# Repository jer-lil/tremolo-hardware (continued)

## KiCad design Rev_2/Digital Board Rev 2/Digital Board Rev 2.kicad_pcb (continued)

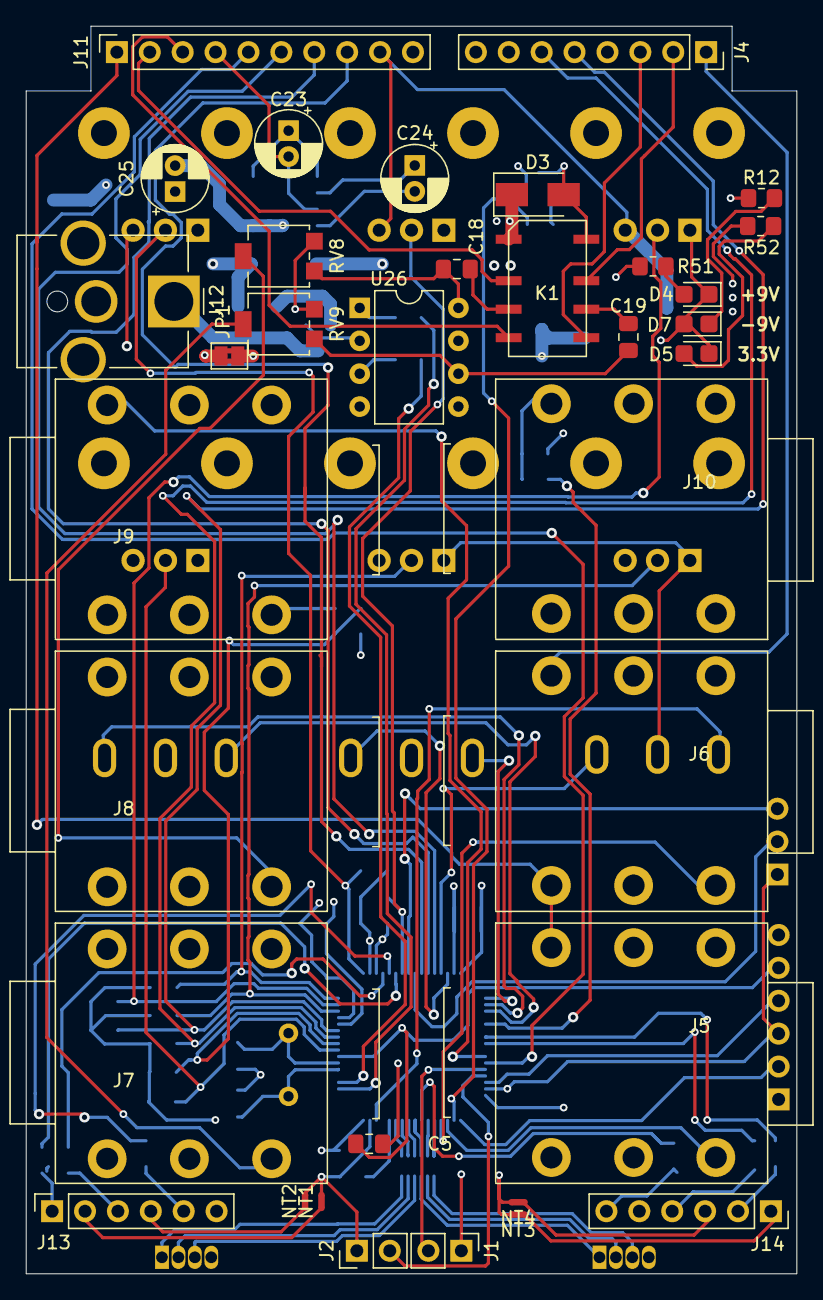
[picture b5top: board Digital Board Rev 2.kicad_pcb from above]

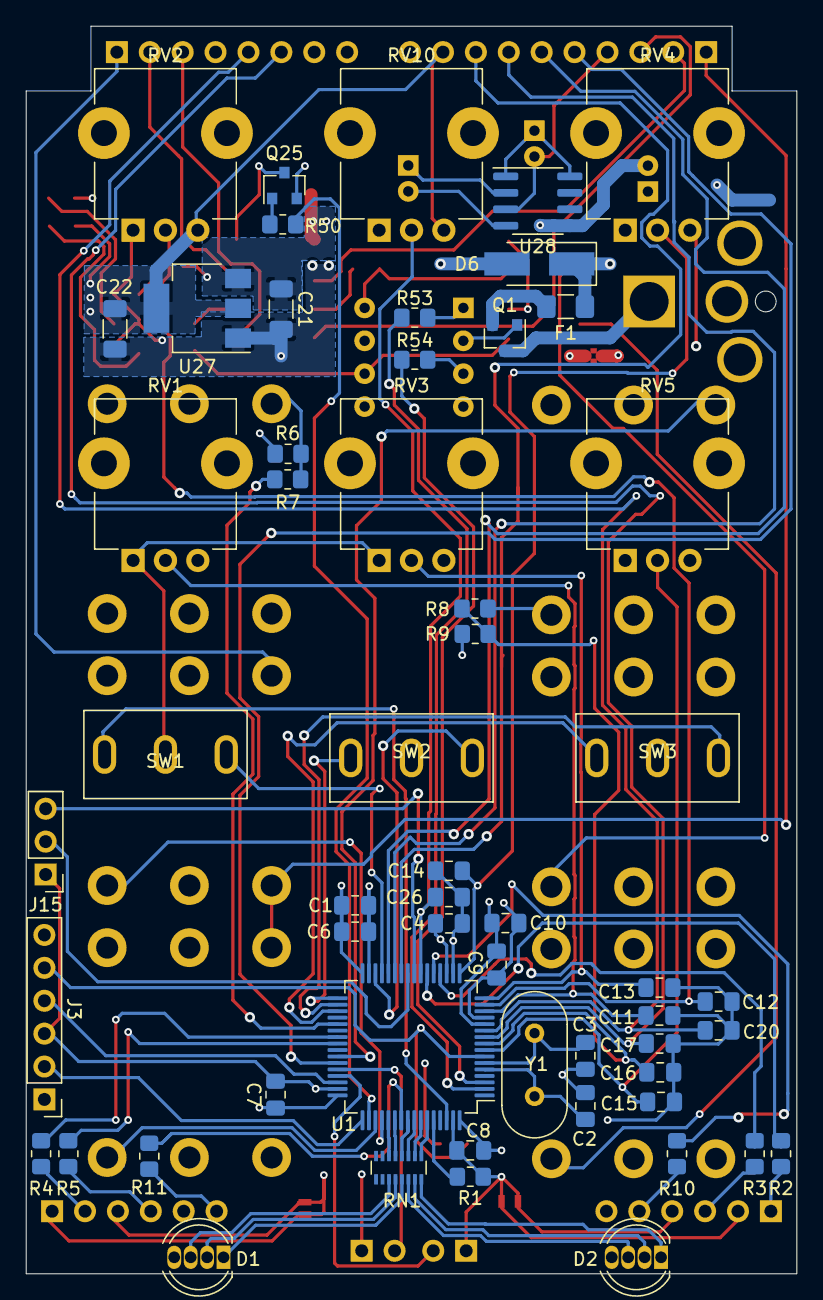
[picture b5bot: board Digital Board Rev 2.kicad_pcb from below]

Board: 4 copper layers, 59.5 x 96.3 mm, 91 parts (56 on the bottom side), 94 nets.

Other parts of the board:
D1, D2: LED_RGBA; LED_D5.0mm-4_RGB
RN1: R_Pack08; R_Array_Convex_8x0602
U26: TLP222A-2; DIP-8_W7.62mm

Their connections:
+3V3: D1.4, D2.4; also elsewhere on the board
/Audio Jacks/CH1_OUT_PRE: U26.8; also elsewhere on the board
/Audio Jacks/CH2_OUT_PRE: U26.6; also elsewhere on the board
/LED1_B: RN1.6; also elsewhere on the board
/LED1_G: RN1.5; also elsewhere on the board
/LED1_R: RN1.4; also elsewhere on the board
/LED2_B: RN1.3; also elsewhere on the board
/LED2_G: RN1.2; also elsewhere on the board
/LED2_R: RN1.1; also elsewhere on the board
/LEDs/B1_R: D1.3, RN1.11
/LEDs/B2_R: D2.3, RN1.14
/LEDs/G1_R: D1.2, RN1.12
/LEDs/G2_R: D2.2, RN1.15
/LEDs/R1_R: D1.1, RN1.13
/LEDs/R2_R: D2.1, RN1.16
GNDA: U26.5, U26.7; also elsewhere on the board
GNDD: U26.2, U26.4; also elsewhere on the board
unnamed 115: U26.1; also elsewhere on the board
unnamed 116: U26.3; also elsewhere on the board

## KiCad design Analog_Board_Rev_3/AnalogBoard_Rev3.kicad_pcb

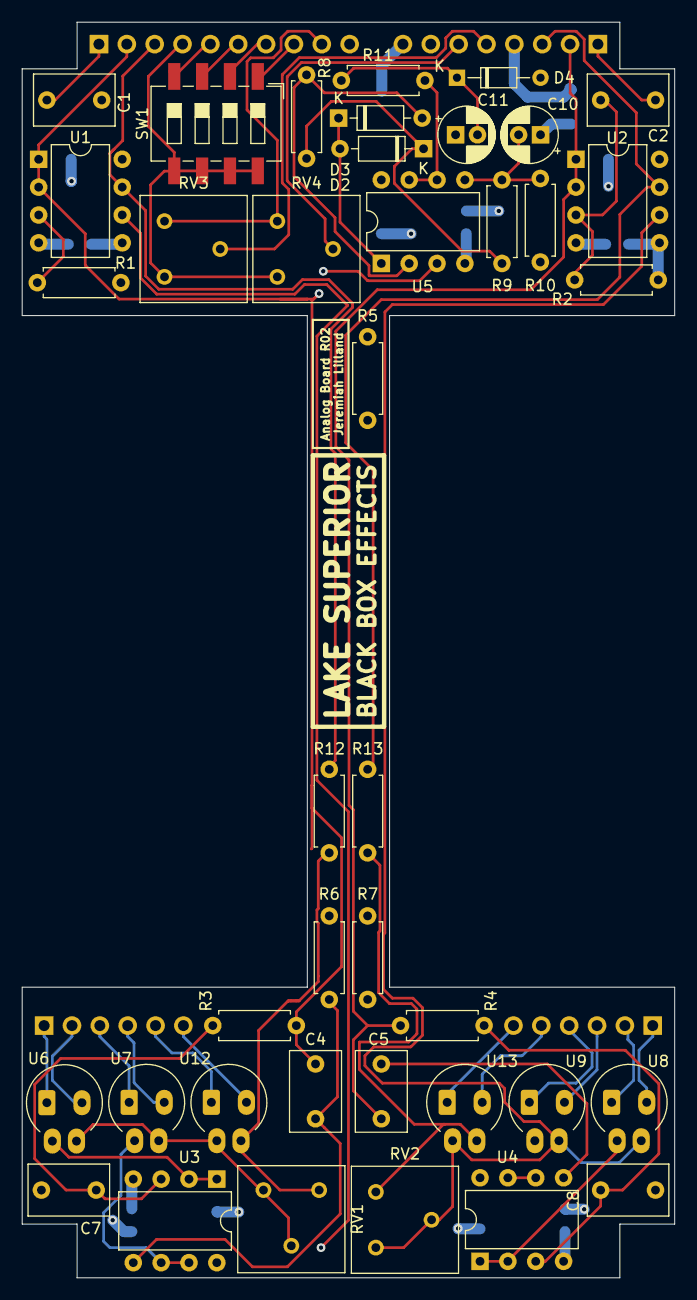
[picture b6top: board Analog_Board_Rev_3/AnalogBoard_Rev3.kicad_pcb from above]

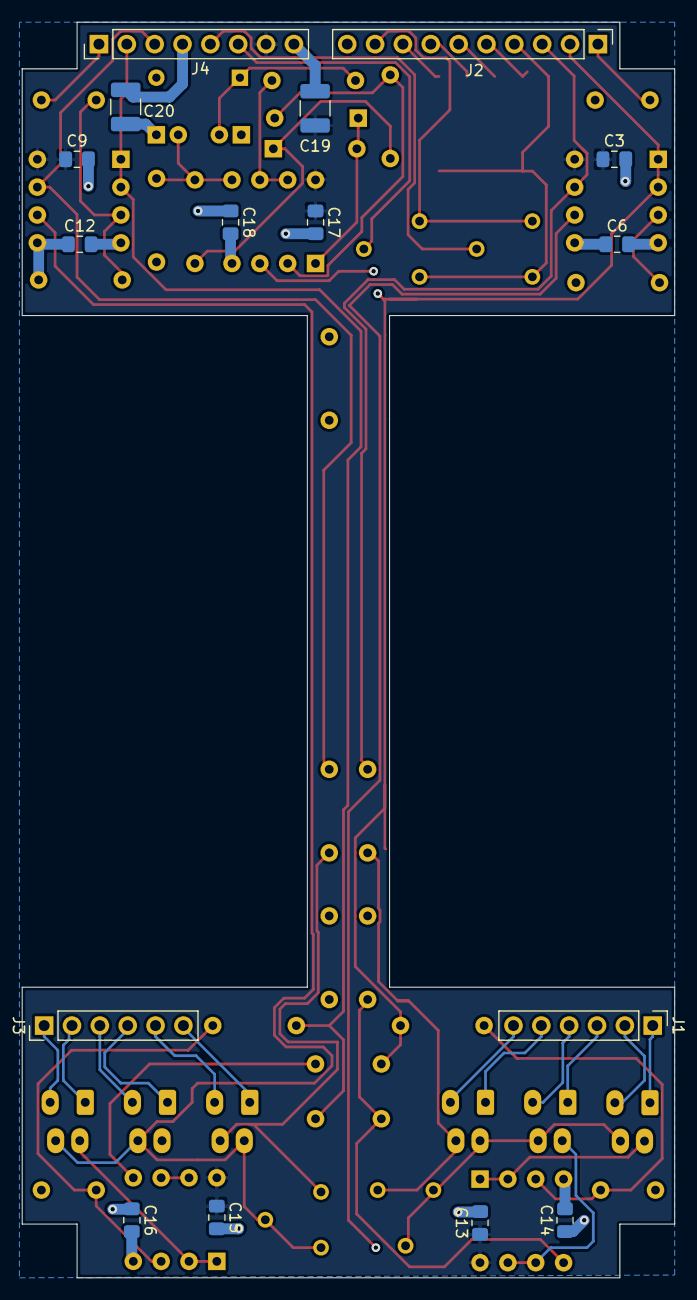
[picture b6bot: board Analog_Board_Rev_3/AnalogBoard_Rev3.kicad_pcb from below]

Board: 4 copper layers, 59.5 x 114.5 mm, 56 parts (16 on the bottom side), 49 nets.

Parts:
C1, C2: 47n; C_Rect_L7.2mm_W4.5mm_P5.00mm_FKS2_FKP2_MKS2_MKP2
C3, C6, C9, C12, C13, C14, C15, C16, C17, C18: 100n; C_0805_2012Metric_Pad1.18x1.45mm_HandSolder
C4, C5, C7, C8: 1n; C_Rect_L7.2mm_W4.5mm_P5.00mm_FKS2_FKP2_MKS2_MKP2
C10: 4.7u; CP_Radial_D5.0mm_P2.00mm
C11: 47u; CP_Radial_D5.0mm_P2.00mm
C19, C20: 10u; C_1210_3225Metric_Pad1.33x2.70mm_HandSolder
D2, D3: 1N914; D_DO-35_SOD27_P7.62mm_Horizontal
D4: D_Zener; D_DO-34_SOD68_P7.62mm_Horizontal
J1, J3: Conn_01x06_Male; PinHeader_1x06_P2.54mm_Vertical
J2: Conn_01x10_Male; PinHeader_1x10_P2.54mm_Vertical
J4: Conn_01x08_Male; PinHeader_1x08_P2.54mm_Vertical
R1, R2: 1M; R_Axial_DIN0207_L6.3mm_D2.5mm_P7.62mm_Horizontal
R3, R4, R6, R7: 470k; R_Axial_DIN0207_L6.3mm_D2.5mm_P7.62mm_Horizontal
R5: 3.3k; R_Axial_DIN0207_L6.3mm_D2.5mm_P7.62mm_Horizontal
R8: 100k; R_Axial_DIN0207_L6.3mm_D2.5mm_P7.62mm_Horizontal
R9: 10k; R_Axial_DIN0207_L6.3mm_D2.5mm_P7.62mm_Horizontal
R10: 47k; R_Axial_DIN0207_L6.3mm_D2.5mm_P7.62mm_Horizontal
R11, R12, R13: 1k; R_Axial_DIN0207_L6.3mm_D2.5mm_P7.62mm_Horizontal
RV1, RV2, RV3, RV4: 50k; Potentiometer_Bourns_3386F_Vertical
SW1: SW_DIP_x04; SW_DIP_SPSTx04_Slide_6.7x11.72mm_W8.61mm_P2.54mm_LowProfile
U1, U2, U3, U4, U5: OPA2134; DIP-8_W7.62mm
U6, U7, U8, U9, U12, U13: NSL-32; Luna_NSL-32_Vertical

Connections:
+3V3: J2.9, RV3.3, RV4.3
+9V: C3.1, C9.1, C13.1, C15.1, C17.1, C19.1, J4.7, U1.8, U2.8, U3.8, U4.8, U5.8
-9V: C6.2, C12.2, C14.2, C16.2, C18.2, C20.2, J4.4, U1.4, U2.4, U3.4, U4.4, U5.4
/CH1_BYP: C4.2, J2.2, R3.1, U1.1, U1.2, U5.3
/CH1_EFF: J2.3, R12.2, U1.7
/CH2_BYP: C5.2, J4.2, R4.1, U2.1, U2.2
/CH2_EFF: J4.3, R13.2, U2.7
/DIP1: J2.8, SW1.1
/DIP2: J2.7, SW1.2
/DIP3: J2.6, SW1.3
/DIP4: J2.5, SW1.4
/ENV_OUT: C11.2, D4.1, R11.2
/IN1: C1.2, J2.1
/IN2: C2.2, J4.1
/LDRA_1: U3.1, U3.2, U6.4
/LDRA_2: RV1.1, RV1.2, U1.6, U6.3, U7.3, U12.4
/LDRB_1: U3.6, U3.7, U7.4
/LDRC_1: U4.1, U4.2, U8.4
/LDRC_2: RV2.1, RV2.2, U2.6, U8.3, U9.3, U13.4
/LDRD_1: U4.6, U4.7, U9.4
/PWM_1: J1.1, U6.1
/PWM_1_RTN: J1.2, U6.2
/PWM_2: J1.3, U7.1
/PWM_2_RTN: J1.4, U7.2
/PWM_3: J3.2, U8.1
/PWM_3_RTN: J3.1, U8.2
/PWM_4: J3.4, U9.1
/PWM_4_RTN: J3.3, U9.2
/PWM_VOL1: J1.5, U12.1
/PWM_VOL1_RTN: J1.6, U12.2
/PWM_VOL2: J3.6, U13.1
/PWM_VOL2_RTN: J3.5, U13.2
/TRIM_1: J4.5, RV3.2
/TRIM_2: J4.6, RV4.2
GND: C3.2, C6.1, C7.1, C8.1, C9.2, C10.1, C11.1, C12.1, C13.2, C14.1, C15.2, C16.1, C17.2, C18.1, C19.2, C20.1, D4.2, J2.10, J4.8, R1.1, R2.1, R5.2, R6.1, R7.1, R10.2, U1.5, U2.5
GNDD: J2.4, RV3.1, RV4.1, SW1.5, SW1.6, SW1.7, SW1.8
unnamed: C1.1, R1.2, U1.3
unnamed: C2.1, R2.2, U2.3
unnamed: C4.1, R6.2, U3.5
unnamed: C5.1, R7.2, U4.5
unnamed: C7.2, R3.2, U3.3
unnamed: C8.2, R4.2, U4.3
unnamed: C10.2, R9.2, R10.1, U5.5
unnamed: D2.1, D3.2, U5.1
unnamed: D2.2, R5.1, R8.1, U5.2
unnamed: D3.1, R8.2, R9.1
unnamed: R11.1, U5.6, U5.7
unnamed: R12.1, RV1.3, U12.3
unnamed: R13.1, RV2.3, U13.3

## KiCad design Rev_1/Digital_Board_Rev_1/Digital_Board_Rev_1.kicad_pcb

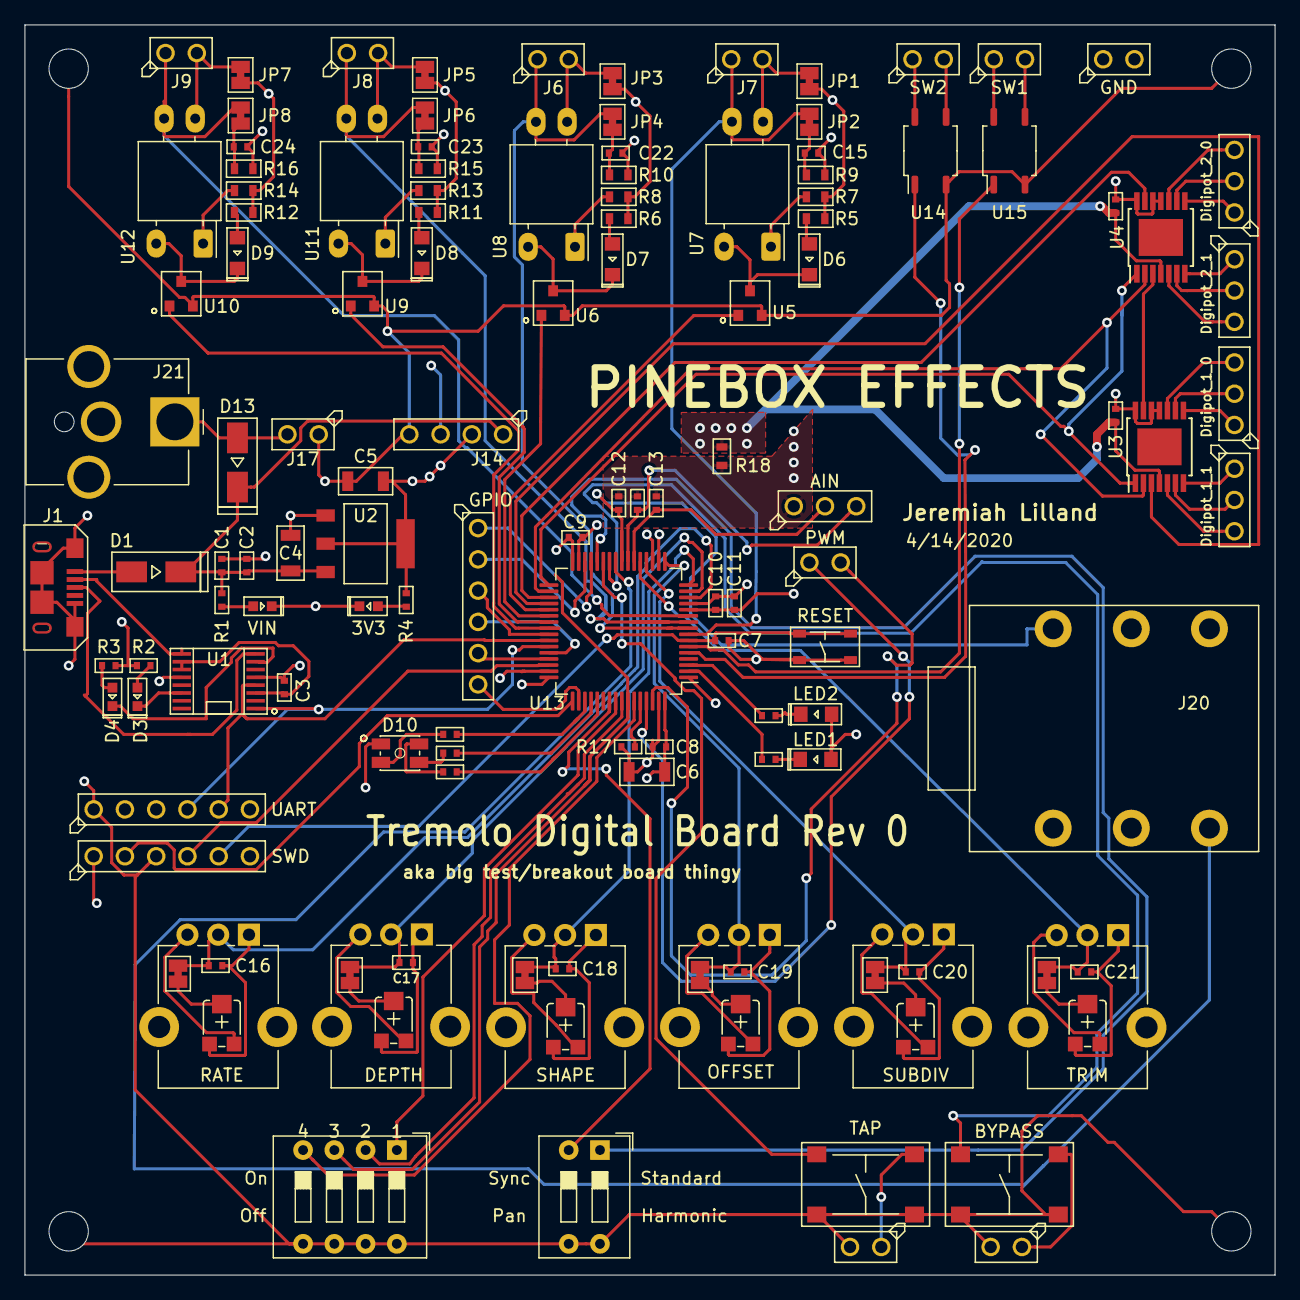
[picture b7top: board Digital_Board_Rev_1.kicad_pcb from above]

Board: 4 copper layers, 101.6 x 101.6 mm, 133 parts (0 on the bottom side), 116 nets.

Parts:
3V3: LED_SINGLE-0603-GREEN; MF_LEDs-LED0603
AIN: CON_01X03_PTH_2.54MM; MF_Connectors-PTH_2.54MM_01X03
BYPASS: TACT_6MM; MF_Switches-TACT6MM
C1, C11: 1uF; MF_Passives-C0402
C2, C3, C7, C8, C9, C12, C13, C14, C16, C17, C18, C19, C20, C21: 0.1uF; MF_Passives-C0402
C4, C5, C6: 10uF; MF_Passives-C1206
C10: 10n; MF_Passives-C0402
C15, C22, C23, C24: 100n; MF_Passives-C0402
D1, D13: DIODES_B140_SMA; MF_Discrete_Semiconductor-SMA
D3, D4: LED_SINGLE-0603-GREEN; MF_LEDs-LED0603
D6, D7, D8, D9: LED_SINGLE-0805-RED; MF_LEDs-LED0805
D10: LED_RGB_CA_PLCC4; MF_LEDs-PLCC4
DEPTH: POTENTIOMETER_10K_TC33; MF_Passives-TC33
Digipot_1_0, Digipot_1_1, Digipot_2_0, Digipot_2_1: CON_01X03_PTH_2.54MM; MF_Connectors-PTH_2.54MM_01X03
GND: VAL**; MF_Connectors-PTH_2.54MM_01X02
GPIO: CON_01X06_PTH_2.54MM; MF_Connectors-PTH_2.54MM_01X06
H1, H2, H3, H4: MountingHole_Pad; MountingHole_3.2mm_M3
J1: USB_MICRO_RIGHT; MF_Connectors-MICROUSB-RIGHT
J6, J7, J8, J9: Conn_01x02_Male; MF_Connectors-PTH_2.54MM_01X02
J13, J17, J22: CON_01X02_PTH_2.54MM; MF_Connectors-PTH_2.54MM_01X02
J14: CON_01X04_PTH_2.54MM; MF_Connectors-PTH_2.54MM_01X04
J20: AudioJack3_Switch; Jack_0.25in_TRS_Switched
J21: Barrel_Jack; BarrelJack_CUI_PJ-063AH_Horizontal_CircularHoles
JP1, JP2, JP3, JP4, JP5, JP6, JP7, JP8, JP9, JP10, JP11, JP12, JP13, JP14: SolderJumper_2_Bridged; SolderJumper-2_P1.3mm_Bridged_Pad1.0x1.5mm
LED1: LED_SINGLE-0805-GREEN; MF_LEDs-LED0805
LED2: LED_SINGLE-0805-RED; MF_LEDs-LED0805
OFFSET: POTENTIOMETER_10K_TC33; MF_Passives-TC33
PWM: CON_01X02_PTH_2.54MM; MF_Connectors-PTH_2.54MM_01X02
R1: 560; MF_Passives-R0402
R2, R3: 330; MF_Passives-R0402
R4: 470; MF_Passives-R0402
R5, R6, R7, R8, R11, R12, R13, R14: 100; MF_Passives-R0603
R9, R10, R15, R16: 10k; MF_Passives-R0603
R17: 10k; MF_Passives-R0402
R18: 0; MF_Passives-R0603
R25, R26, R27: 100; MF_Passives-R0402
R28, R29: 47; MF_Passives-R0402
RATE: POTENTIOMETER_10K_TC33; MF_Passives-TC33
RESET: TACT_4.2MM; MF_Switches-TACT4.2MM
RV1, RV2, RV3, RV4, RV5, RV6: 10k; Potentiometer_Alpha_RD901F-40-00D_Single_Vertical_CircularH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
SHAPE: POTENTIOMETER_10K_TC33; MF_Passives-TC33
SUBDIV: POTENTIOMETER_10K_TC33; MF_Passives-TC33
SW1: SW_DIP_x04; SW_DIP_SPSTx04_Slide_9.78x12.34mm_W7.62mm_P2.54mm
SW1#2, SW2#2: CON_01X02_PTH_2.54MM; MF_Connectors-PTH_2.54MM_01X02
SW2: SW_DIP_x02; SW_DIP_SPSTx02_Slide_9.78x7.26mm_W7.62mm_P2.54mm
SWD: CON_01X06_PTH_2.54MM; MF_Connectors-PTH_2.54MM_01X06
TAP: TACT_6MM; MF_Switches-TACT6MM
TRIM: POTENTIOMETER_10K_TC33; MF_Passives-TC33
U1: FT230XS-R; MF_IC_Digital-SSOP16
U2: NCP1117LPST33T3G; MF_IC_Power-SOT-223-3
U3, U4: MCP42050; TSSOP-14-1EP_4.4x5mm_P0.65mm
U5, U6, U9, U10: NPN_BJTMMBT3904_SOT-23-3; MF_Discrete_Semiconductor-SOT-23-3
U7, U8, U11, U12: NSL-32; Luna_NSL-32
U13: STM32F030RCTx; LQFP-64_10x10mm_P0.5mm
U14, U15: CPC1017N; SOP-4_3.8x4.1mm_P2.54mm
UART: CON_01X06_PTH_2.54MM; MF_Connectors-PTH_2.54MM_01X06
VIN: LED_SINGLE-0603-GREEN; MF_LEDs-LED0603

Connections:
+3V3: C5.1, C6.1, C8.1, C9.1, C10.1, C11.1, D10.1, DEPTH.3, J14.2, J20.R, JP1.1, JP3.1, JP5.1, JP7.1, LED1.ANOD, LED2.ANOD, OFFSET.3, R2.1, R3.1, R4.1, R5.1, R6.1, R7.1, R8.1, R11.1, R12.1, R13.1, R14.1, RATE.3, RV1.3, RV2.3, RV3.3, RV4.3, RV5.3, RV6.3, SHAPE.3, SUBDIV.3, SWD.1, TRIM.3, U1.12, U2.1, U2.3, U3.11, U3.12, U3.14, U4.11, U4.12, U4.14, U13.1, U13.13, U13.19, U13.32, U13.48, U13.64
+9V: D13.ANOD, J17.2, J21.1
/Digipots/CS: U3.1, U4.1, U13.33
/Digipots/SCK: U3.2, U4.2, U13.34
/Digipots/SI: U4.13, U13.35
/Digipots/SO: U3.3, U13.36
/Digipots/SO1_SI2: U3.13, U4.3
/MCU/BYPASS: BYPASS.1, U13.26
/MCU/DEPTH: C17.1, JP10.1, RV2.2, U13.15
/MCU/EXP: C12.1, J20.T, U13.24
/MCU/EXP_SW: J20.SN, U13.25
/MCU/GPIO_1: GPIO.1, U13.29
/MCU/GPIO_2: GPIO.2, U13.30
/MCU/GPIO_3: GPIO.3, U13.41
/MCU/GPIO_4: GPIO.4, U13.44
/MCU/GPIO_5: GPIO.5, U13.45
/MCU/GPIO_6: GPIO.6, U13.50
/MCU/GP_AIN1: AIN.2, C13.1, U13.22
/MCU/GP_AIN2: AIN.3, C14.1, U13.23
/MCU/GP_PWM1: PWM.1, U13.61
/MCU/GP_PWM2: PWM.2, U13.62
/MCU/LDRV_1: J7.1, JP2.1, U7.3, U13.8
/MCU/LDRV_2: J6.1, JP4.1, U8.3, U13.9
/MCU/LDRV_3: J8.1, JP6.1, U11.3, U13.10
/MCU/LDRV_4: J9.1, JP8.1, U12.3, U13.11
/MCU/NRST: C7.1, RESET.1, RESET.2, SWD.5, U13.7
/MCU/OFFSET: C19.1, JP12.1, RV4.2, U13.17
/MCU/PWM1: U5.1, U13.37
/MCU/PWM2: U6.1, U13.38
/MCU/PWM3: U9.1, U13.39
/MCU/PWM4: U10.1, U13.40
/MCU/RATE: C16.1, JP9.1, RV1.2, U13.14
/MCU/RXD: U1.1, U13.43, UART.4
/MCU/SHAPE: C18.1, JP11.1, RV3.2, U13.16
/MCU/SUBDIV: C20.1, JP13.1, RV5.2, U13.20
/MCU/SW1_1: SW2#2.1, U14.4
/MCU/SW1_2: SW2#2.2, U14.3
/MCU/SW1_CTL: U13.5, U14.1
/MCU/SW2_1: SW1#2.1, U15.4
/MCU/SW2_2: SW1#2.2, U15.3
/MCU/SW2_CTL: U13.6, U15.1
/MCU/SWCLK: SWD.2, U13.49
/MCU/SWDIO: SWD.4, U13.46
/MCU/TAP: TAP.1, U13.27
/MCU/TRIM: C21.1, JP14.1, RV6.2, U13.21
/MCU/TXD: U1.4, U13.42, UART.5
/Power_USB/USBDM: J1.2, U1.9
/Power_USB/USBDP: J1.3, U1.8
GNDA: AIN.1, C10.2, C11.2, C12.2, C13.2, C14.2, C15.2, C16.2, C17.2, C18.2, C19.2, C20.2, C21.2, C22.2, C23.2, C24.2, DEPTH.1, GND.1, GND.2, J14.3, J20.S, OFFSET.1, R9.2, R10.2, R15.2, R16.2, R18.1, RATE.1, RV1.1, RV2.1, RV3.1, RV4.1, RV5.1, RV6.1, SHAPE.1, SUBDIV.1, TRIM.1, U13.12
GNDD: 3V3.CATH, BYPASS.3, BYPASS.4, C1.2, C2.2, C3.2, C4.2, C5.2, C6.2, C7.2, C8.2, C9.2, J1.5, J1.S1, J1.S2, J1.S3, J1.S4, J1.S5, J1.S6, J13.2, J14.4, J17.1, J21.2, J22.2, R17.2, R18.2, RESET.3, RESET.4, SW1.5, SW1.6, SW1.7, SW1.8, SW2.3, SW2.4, SWD.3, TAP.3, TAP.4, U1.5, U2.2, U3.4, U4.4, U5.2, U6.2, U9.2, U10.2, U13.18, U13.31, U13.47, U13.63, U14.2, U15.2, UART.1, VIN.CATH
unnamed: C3.1, U1.3, U1.10, U1.11
unnamed: C15.1, JP2.2, R9.1
unnamed: C22.1, JP4.2, R10.1
unnamed: C23.1, JP6.2, R15.1
unnamed: C24.1, JP8.2, R16.1
unnamed: D1.ANOD, J1.1
unnamed: R1.2, VIN.ANOD
unnamed: D3.ANOD, R2.2
unnamed: D3.CATH, U1.14
unnamed: D4.ANOD, R3.2
unnamed: D4.CATH, U1.7
unnamed: 3V3.ANOD, R4.2
unnamed: D6.ANOD, R5.2
unnamed: D6.CATH, U5.3, U7.2
unnamed: D7.ANOD, R6.2
unnamed: D7.CATH, U6.3, U8.2
unnamed: D8.ANOD, R11.2
unnamed: D8.CATH, U9.3, U11.2
unnamed: D9.ANOD, R12.2
unnamed: D9.CATH, U10.3, U12.2
unnamed: D10.2, R27.2
unnamed: D10.3, R28.2
unnamed: D10.4, R29.2
unnamed: LED1.CATH, R25.2
unnamed: LED2.CATH, R26.2
unnamed: Digipot_1_0.1, U3.8
unnamed: Digipot_1_0.2, U3.9
unnamed: Digipot_1_0.3, U3.10
unnamed: Digipot_1_1.1, U3.7
unnamed: Digipot_1_1.2, U3.6
unnamed: Digipot_1_1.3, U3.5
unnamed: Digipot_2_0.1, U4.8
unnamed: Digipot_2_0.2, U4.9
unnamed: Digipot_2_0.3, U4.10
unnamed: Digipot_2_1.1, U4.7
unnamed: Digipot_2_1.2, U4.6
unnamed: Digipot_2_1.3, U4.5
unnamed: J6.2, JP3.2, U8.4
unnamed: J7.2, JP1.2, U7.4
unnamed: J8.2, JP5.2, U11.4
unnamed: J9.2, JP7.2, U12.4
unnamed: BYPASS.2, J13.1
unnamed: J22.1, TAP.2
unnamed: JP9.2, RATE.2
unnamed: DEPTH.2, JP10.2
unnamed: JP11.2, SHAPE.2
unnamed: JP12.2, OFFSET.2
unnamed: JP13.2, SUBDIV.2
unnamed: JP14.2, TRIM.2
unnamed: R7.2, U7.1
unnamed: R8.2, U8.1
unnamed: R13.2, U11.1
unnamed: R14.2, U12.1
unnamed: R17.1, U13.60
unnamed: R25.1, U13.2
unnamed: R26.1, U13.3
unnamed: R27.1, U13.51
unnamed: R28.1, U13.52
unnamed: R29.1, U13.53
unnamed: SW1.1, U13.56
unnamed: SW1.2, U13.57
unnamed: SW1.3, U13.58
unnamed: SW1.4, U13.59
unnamed: SW2.1, U13.28
unnamed: SW2.2, U13.55
VBUS: C1.1, C2.1, C4.1, D1.CATH, D13.CATH, J14.1, R1.1, U2.4

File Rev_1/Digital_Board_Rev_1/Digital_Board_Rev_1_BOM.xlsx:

Id | Designator | Package | MPN | Quantity | Designation | Supplier and ref | _1
1 | J1 | MF_Connectors-MICROUSB-RIGHT |  | 1 | USB_MICRO_RIGHT
2 | U1 | MF_IC_Digital-SSOP16 |  | 1 | FT230XS-R
3 | REF**,REF**,C12,C21,C20,C19,C18,C17,C16,C14,C13,C9,C8,C7,C3,C2 | MF_Passives-C0402 |  | 16 | 0.1uF
4 | GND | MF_Connectors-PTH_2.54MM_01X02 |  | 1 | VAL**
5 | DEPTH,TRIM,SUBDIV,OFFSET,SHAPE,RATE | MF_Passives-TC33 | TC33X-2-103E | 6 | POTENTIOMETER_10K_TC33
6 | JP8,JP7,JP6,JP5,JP4,JP3,JP2,JP1,JP14,JP13,JP12,JP11,JP10,JP9 | SolderJumper-2_P1.3mm_Bridged_Pad1.0x1.5mm |  | 14 | SolderJumper_2_Bridged
7 | J22,J13,SW1,SW2,J17,PWM | MF_Connectors-PTH_2.54MM_01X02 |  | 6 | CON_01X02_PTH_2.54MM
8 | H4,H3,H2,H1 | MountingHole_3.2mm_M3 |  | 4 | MountingHole_Pad
9 | C24,C23,C22,C15 | MF_Passives-C0402 |  | 4 | 100n
10 | J21 | BarrelJack_CUI_PJ-063AH_Horizontal_CircularHoles |  | 1 | Barrel_Jack
11 | U15,U14 | SOP-4_3.8x4.1mm_P2.54mm |  | 2 | CPC1017N
12 | J20 | Jack_0.25in_TRS_Switched |  | 1 | AudioJack3_Switch
13 | U13 | LQFP-64_10x10mm_P0.5mm | STM32F030RCT6TR | 1 | STM32F030RCTx
14 | U12,U11,U8,U7 | Luna_NSL-32 |  | 4 | NSL-32
15 | U10,U9,U6,U5 | MF_Discrete_Semiconductor-SOT-23-3 |  | 4 | NPN_BJTMMBT3904_SOT-23-3
16 | U4,U3 | TSSOP-14-1EP_4.4x5mm_P0.65mm |  | 2 | MCP42050
17 | U2 | MF_IC_Power-SOT-223-3 |  | 1 | NCP1117LPST33T3G
18 | RESET | MF_Switches-TACT4.2MM |  | 1 | TACT_4.2MM
19 | BYPASS,TAP | MF_Switches-TACT6MM |  | 2 | TACT_6MM
20 | SW2 | SW_DIP_SPSTx02_Slide_9.78x7.26mm_W7.62mm_P2.54mm |  | 1 | SW_DIP_x02
21 | SW1 | SW_DIP_SPSTx04_Slide_9.78x12.34mm_W7.62mm_P2.54mm |  | 1 | SW_DIP_x04
22 | RV6,RV5,RV4,RV3,RV2,RV1 | Potentiometer_Alpha_RD901F-40-00D_Single_Vertical_CircularHoles |  | 6 | 10k
23 | R29,R28 | MF_Passives-R0402 |  | 2 | 47
24 | R27,R26,R25 | MF_Passives-R0402 |  | 3 | 100
25 | R18 | MF_Passives-R0603 |  | 1 | 0
26 | R17 | MF_Passives-R0402 |  | 1 | 10k
27 | R16,R15,R10,R9 | MF_Passives-R0603 |  | 4 | 10k
28 | R14,R13,R12,R11,R8,R7,R6,R5 | MF_Passives-R0603 |  | 8 | 100
29 | R4 | MF_Passives-R0402 |  | 1 | 470
30 | R3,R2 | MF_Passives-R0402 |  | 2 | 330
31 | R1 | MF_Passives-R0402 |  | 1 | 560
32 | GPIO,SWD,UART | MF_Connectors-PTH_2.54MM_01X06 |  | 3 | CON_01X06_PTH_2.54MM
33 | J14 | MF_Connectors-PTH_2.54MM_01X04 |  | 1 | CON_01X04_PTH_2.54MM
34 | AIN,Digipot_2_1,Digipot_2_0,Digipot_1_1,Digipot_1_0 | MF_Connectors-PTH_2.54MM_01X03 |  | 5 | CON_01X03_PTH_2.54MM
35 | J9,J8,J7,J6 | MF_Connectors-PTH_2.54MM_01X02 |  | 4 | Conn_01x02_Male
36 | D13,D1 | MF_Discrete_Semiconductor-SMA |  | 2 | DIODES_B140_SMA
37 | LED2,D9,D8,D7,D6 | MF_LEDs-LED0805 |  | 5 | LED_SINGLE-0805-RED
38 | LED1 | MF_LEDs-LED0805 |  | 1 | LED_SINGLE-0805-GREEN
39 | D10 | MF_LEDs-PLCC4 |  | 1 | LED_RGB_CA_PLCC4
40 | 3V3,D4,D3,VIN | MF_LEDs-LED0603 |  | 4 | LED_SINGLE-0603-GREEN
41 | C11,C1 | MF_Passives-C0402 |  | 2 | 1uF
42 | C10 | MF_Passives-C0402 |  | 1 | 10n
43 | C6,C5,C4 | MF_Passives-C1206 |  | 3 | 10uF

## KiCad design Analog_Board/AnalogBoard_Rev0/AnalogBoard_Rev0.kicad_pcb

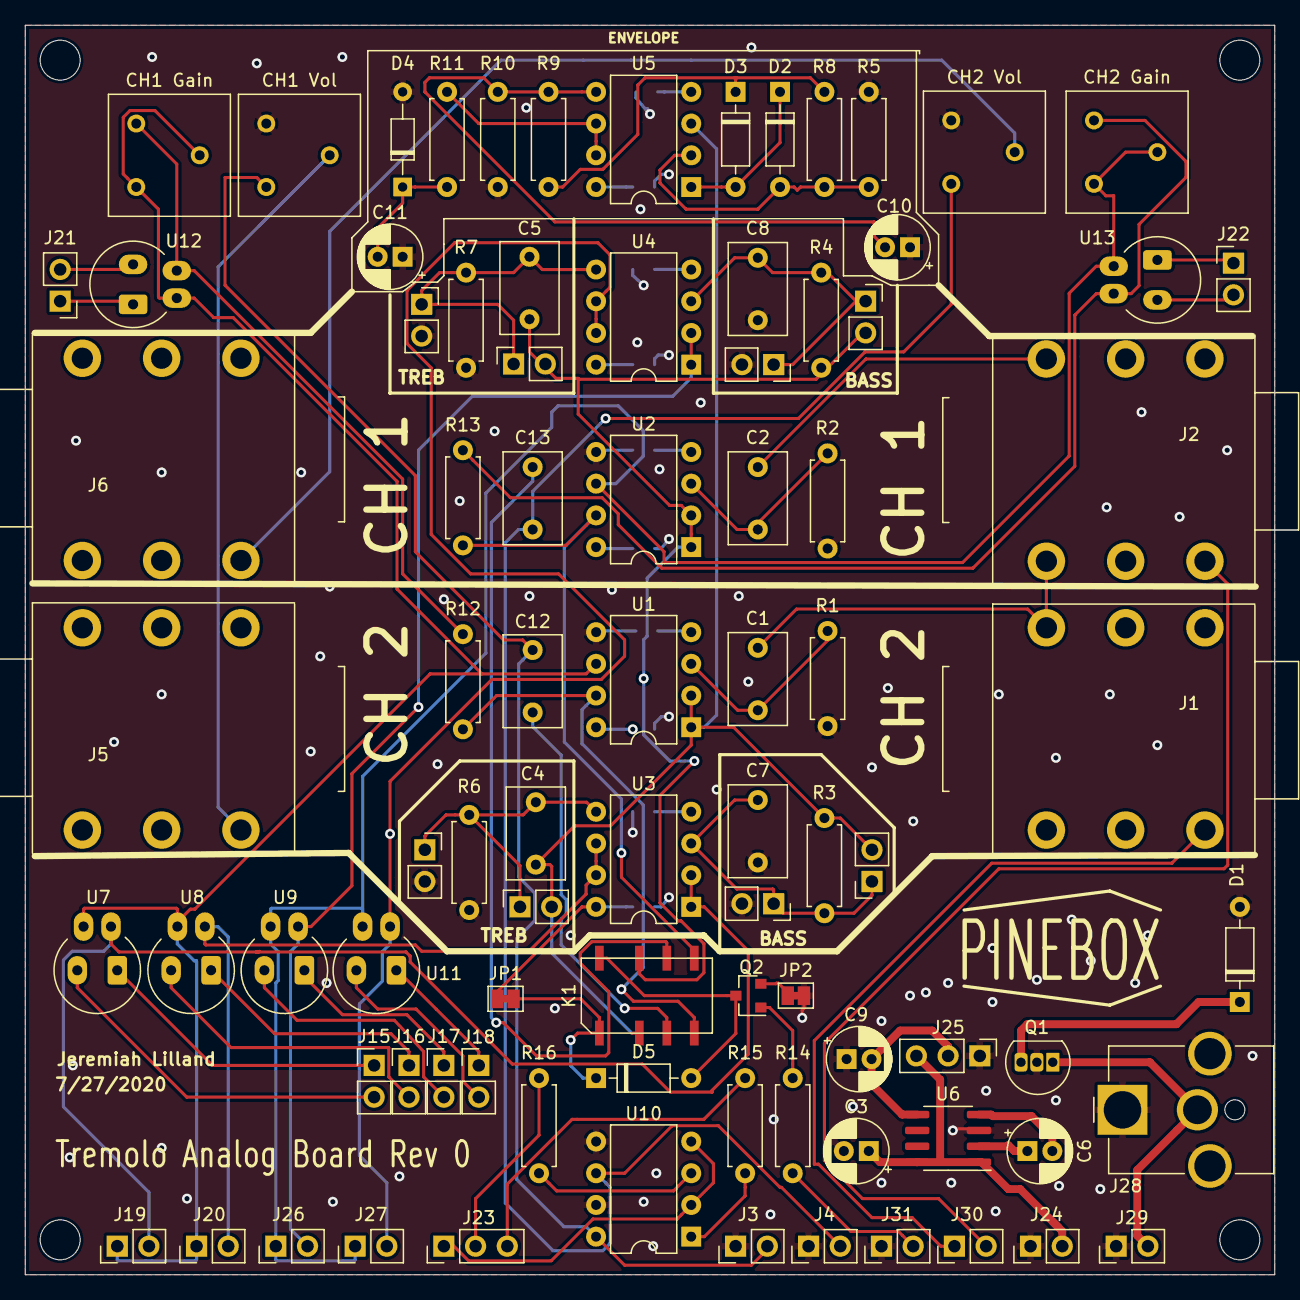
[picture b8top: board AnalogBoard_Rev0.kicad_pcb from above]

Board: 4 copper layers, 100.1 x 100.1 mm, 101 parts (0 on the bottom side), 62 nets.

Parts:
C1, C2: 47n; C_Rect_L7.2mm_W4.5mm_P5.00mm_FKS2_FKP2_MKS2_MKP2
C3, C6, C9: 100uF; CP_Radial_D5.0mm_P2.00mm
C4, C5, C7, C8: 1n; C_Rect_L7.2mm_W4.5mm_P5.00mm_FKS2_FKP2_MKS2_MKP2
C10: 4.7u; CP_Radial_D5.0mm_P2.00mm
C11: 47u; CP_Radial_D5.0mm_P2.00mm
C12, C13: 470n; C_Rect_L7.2mm_W4.5mm_P5.00mm_FKS2_FKP2_MKS2_MKP2
C14, C15, C16, C17, C18, C19, C20, C21, C22, C23: 100n; C_0603_1608Metric_Pad1.05x0.95mm_HandSolder
CH1 Gain, CH1 Vol, CH2 Gain, CH2 Vol: 50k; Potentiometer_Bourns_3386F_Vertical
D1: 10.2; D_DO-35_SOD27_P7.62mm_Horizontal
D2, D3: 1N914; D_DO-35_SOD27_P7.62mm_Horizontal
D4: D_Zener; D_DO-34_SOD68_P7.62mm_Horizontal
D5: B120-E3; D_DO-35_SOD27_P7.62mm_Horizontal
H1, H2, H3, H4: MountingHole; MountingHole_3.2mm_M3
J1, J2, J5, J6: AudioJack3_Switch; Jack_0.25in_TRS_Switched
J3, J4, J15, J16, J17, J18, J19, J20, J21, J22, J24, J26, J27, J29, J30, J31: Conn_01x02_Male; PinHeader_1x02_P2.54mm_Vertical
J7, J8, J9, J10, J11, J12, J13, J14: Conn_01x02_Female; PinSocket_1x02_P2.54mm_Vertical
J23, J25: Conn_01x03_Male; PinHeader_1x03_P2.54mm_Vertical
J28: Barrel_Jack_MountingPin; BarrelJack_CUI_PJ-063AH_Horizontal_CircularHoles
JP1, JP2: JMP_NC; SolderJumper-2_P1.3mm_Bridged_Pad1.0x1.5mm
K1: IM05; Relay_DPDT_NL_TE_IM05GR
Q1: Q_PMOS_DGS; TO-92L_Inline
Q2: MMBT3904; SOT-23
R1, R2: 1M; R_Axial_DIN0207_L6.3mm_D2.5mm_P7.62mm_Horizontal
R3, R4, R6, R7: 470k; R_Axial_DIN0207_L6.3mm_D2.5mm_P7.62mm_Horizontal
R5: 3.3k; R_Axial_DIN0207_L6.3mm_D2.5mm_P7.62mm_Horizontal
R8: 100k; R_Axial_DIN0207_L6.3mm_D2.5mm_P7.62mm_Horizontal
R9: 10k; R_Axial_DIN0207_L6.3mm_D2.5mm_P7.62mm_Horizontal
R10: 47k; R_Axial_DIN0207_L6.3mm_D2.5mm_P7.62mm_Horizontal
R11, R12, R13: 1k; R_Axial_DIN0207_L6.3mm_D2.5mm_P7.62mm_Horizontal
R14: 4.7k; R_Axial_DIN0207_L6.3mm_D2.5mm_P7.62mm_Horizontal
R15, R16: 630; R_Axial_DIN0207_L6.3mm_D2.5mm_P7.62mm_Horizontal
U1, U2, U3, U4, U5: OPA2134; DIP-8_W7.62mm
U6: TC7662Bx0A; SOIC-8_3.9x4.9mm_P1.27mm
U7, U8, U9, U11, U12, U13: NSL-32; Luna_NSL-32_Vertical
U10: TLP222A-2; DIP-8_W7.62mm

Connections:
+9V: C3.1, C14.2, C16.2, C18.2, C20.2, C22.2, D1.1, J24.2, J25.3, JP1.2, Q1.3, U1.8, U2.8, U3.8, U4.8, U5.8, U6.1, U6.8
-9V: C9.2, C15.1, C17.1, C19.1, C21.1, C23.1, J25.2, U1.4, U2.4, U3.4, U4.4, U5.4, U6.5
/ENV_OUT: C11.2, D4.1, R11.2
/IN1: C1.2, J1.T, J2.TN
/IN2: C2.2, J2.T
/LDRA_1: J19.2, U3.1, U3.2, U7.4
/LDRA_2: CH1 Gain.1, CH1 Gain.2, J19.1, J20.1, U1.6, U7.3, U8.3, U12.4
/LDRB_1: J20.2, U3.6, U3.7, U8.4
/LDRC_1: J26.2, U4.1, U4.2, U9.4
/LDRC_2: CH2 Gain.1, CH2 Gain.2, J26.1, J27.1, U2.6, U9.3, U11.3, U13.4
/LDRD_1: J27.2, U4.6, U4.7, U11.4
/MUTE1: J23.3, R15.1
/MUTE2: J23.2, R16.1
/OUT1: CH1 Vol.2, J5.T
/OUT2: CH2 Vol.2, J6.T
/PWR_IN: J28.2, J29.2, Q1.1
/RLY_SET: J31.2, R14.1
/SW_STREO_1: J1.SN, J30.1
/SW_STREO_2: J2.SN, J30.2
GND: C3.2, C7.1, C8.1, C9.1, C10.1, C11.1, C14.1, C15.2, C16.1, C17.2, C18.1, C19.2, C20.1, C21.2, C22.1, C23.2, CH1 Vol.3, CH2 Vol.3, D1.2, D4.2, J3.1, J4.1, J11.2, J12.2, J13.2, J14.2, J24.1, J25.1, J28.1, J28.MP, J29.1, J31.1, JP2.1, Q1.2, R1.1, R2.1, R5.2, R6.1, R7.1, R10.2, U1.5, U2.5, U6.3, U10.5, U10.7
GNDD: J23.1, U10.2, U10.4
unnamed: C1.1, R1.2, U1.3
unnamed: C2.1, R2.2, U2.3
unnamed: C4.1, J8.1, J11.1, R6.2, U3.5
unnamed: C4.2, J7.2, J8.2, K1.2, R3.1, U1.1, U1.2, U5.3
unnamed: C5.1, J10.1, J12.1, R7.2, U4.5
unnamed: C5.2, J9.2, J10.2, K1.7, R4.1, U2.1, U2.2
unnamed: C6.1, U6.2
unnamed: C6.2, U6.4
unnamed: C7.2, J7.1, J13.1, R3.2, U3.3
unnamed: C8.2, J9.1, J14.1, R4.2, U4.3
unnamed: C10.2, R9.2, R10.1, U5.5
unnamed: C12.1, CH1 Vol.1, J3.2, U10.8
unnamed: C12.2, K1.3
unnamed: C13.1, CH2 Vol.1, J4.2, U10.6
unnamed: C13.2, K1.6
unnamed: D2.1, D3.2, U5.1
unnamed: D2.2, R5.1, R8.1, U5.2
unnamed: D3.1, R8.2, R9.1
unnamed: D5.1, JP1.1, K1.1
unnamed: D5.2, K1.8, Q2.3
unnamed: J15.1, U7.1
unnamed: J15.2, U7.2
unnamed: J16.1, U8.1
unnamed: J16.2, U8.2
unnamed: J17.1, U9.1
unnamed: J17.2, U9.2
unnamed: J18.1, U11.1
unnamed: J18.2, U11.2
unnamed: J21.1, U12.1
unnamed: J21.2, U12.2
unnamed: J22.1, U13.1
unnamed: J22.2, U13.2
unnamed: JP2.2, Q2.2
unnamed: K1.4, R12.2, U1.7
unnamed: K1.5, R13.2, U2.7
unnamed: Q2.1, R14.2
unnamed: R11.1, U5.6, U5.7
unnamed: CH1 Gain.3, R12.1, U12.3
unnamed: CH2 Gain.3, R13.1, U13.3
unnamed: R15.2, U10.1
unnamed: R16.2, U10.3

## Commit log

2019-07-07 First commit. Schematic done?
2019-07-14 commit test
    Multiline?
2020-05-26 Started analog board schematic. Added SPICE files
2020-10-04 analog board done awhile ago lol
2021-11-07 r2 boards released, finally pushing
2023-06-14 reorg pt 1
    Reorganizing, deleted a bunch of stuff. Probably will reorg some more
2023-06-14 moved everything out of Boards folder
2025-03-27 Added projects for V3 boards
    Made V3 projects, started with a few changes in both schematics.
    Migrated to KiCad 9.0.
    Repo needs a bit of reorg
2025-03-27 Update .gitignore
    to exclude Kicad files
2025-03-27 Removed unnecessary files, added old gerber outputs
    Updated repo to remove files now ignored by updated .gitignore file.
2025-03-27 Moved all projects into "Rev_X/" folders
2025-04-27 Pivoting to Passive Jack Boards
    Finalized layout for input/output Jack Boards, which are now completely passive and connected with board-to-board connectors. Schematics are not updated yet, just figuring out placement/dimensions.
2025-05-02 Added analog board back, switched to Jacks on Bottom
    Added analog board mezzanine back to fit everything. Finalized decision on jack boards; jacks on bottom, wire to board connectors between jack boards and digital board. Tentative board outlines defin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
2026-01-04 Backing up before windows crash debug
